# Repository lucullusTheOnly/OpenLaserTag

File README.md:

# OpenLaserTag
OperLaserTag is a DIY system for the popular game lasertag. I have designed it for high flexibility for game modes. With this article series and a little knowledge about electronics with microcontrollers like the Arduino you should be able to build your own lasertag system.
The work on this project isn't finished jet and I would be glad to receive some honest hints about what the system should be able to do and how this can be accomplished.

The System consists of the Arduino-based tagger, which is connected to a smartphone via bluetooth. The tagger uses an infrared LED and a lens to send a beam of modulated IR-light in the direction the tagger is pointed to. This works similar to normal IR-remotes, for example for your TV. The tagger is connected to a number of receiver modules, which are located on a vest, so that you can be hit by other players with their tagger. The Arduino informs the smartphone whenever something happens via a bluetooth-serial module and the smartphone does all the management of the game.

At the current state the tagger systems of different players don't have any contact. I designed the system, so that the game follows rules written in a XML-file and will end in a given time limit. This gives great flexibility, because you don't have to set up a communication system over the whole game field (which may be quite big). But this feature (over a limited range) could be added using 433MHz transmission modules.

For more information please visit the Wiki.

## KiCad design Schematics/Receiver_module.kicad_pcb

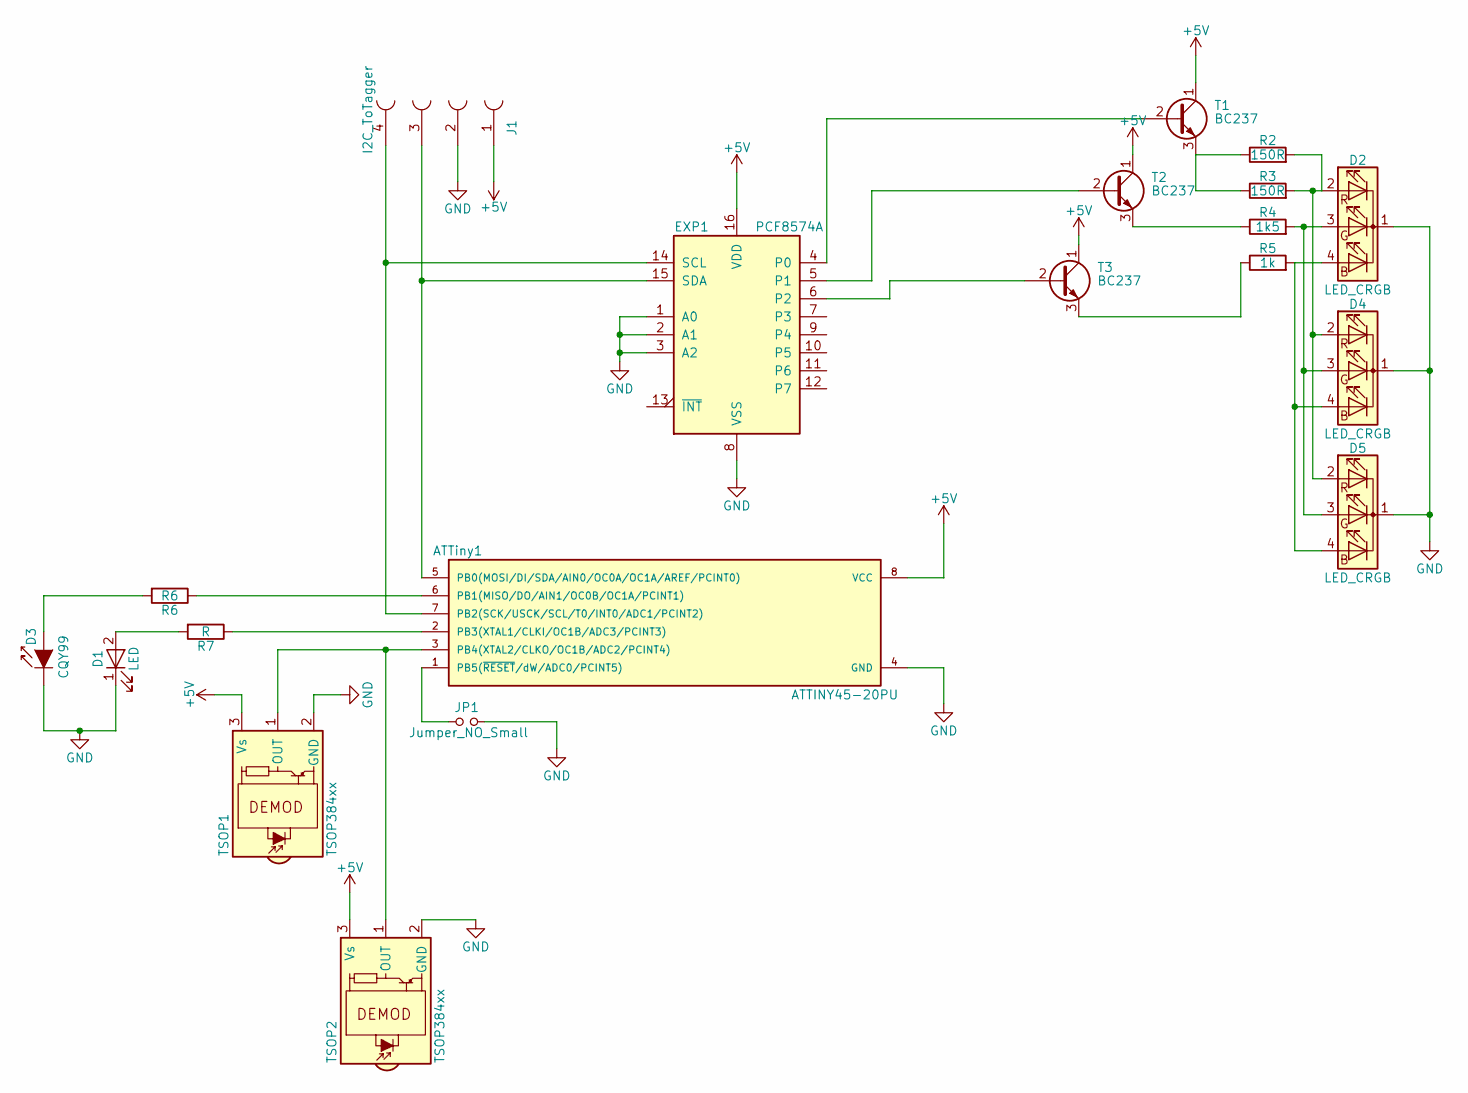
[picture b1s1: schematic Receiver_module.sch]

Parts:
ATTiny1: ATTINY45-20PU; DIP-8_W7.62mm
D1: LED; LED_D5.0mm_FlatTop
D2, D4, D5: LED_CRGB; LED_D5.0mm-4
D3: CQY99; LED_D5.0mm_FlatTop
EXP1: PCF8574A; DIP-16_W7.62mm_Socket
J1: I2C_ToTagger; SDL-104-X-XX_2x02
JP1: Jumper_NO_Small; Pin_Header_Straight_1x02_Pitch2.54mm
R2, R3: 150R; R_Axial_DIN0204_L3.6mm_D1.6mm_P2.54mm_Vertical
R4: 1k5; R_Axial_DIN0204_L3.6mm_D1.6mm_P2.54mm_Vertical
R5: 1k; R_Axial_DIN0204_L3.6mm_D1.6mm_P2.54mm_Vertical
R6: R6; R_Axial_DIN0204_L3.6mm_D1.6mm_P2.54mm_Vertical
R7: R; R_Axial_DIN0204_L3.6mm_D1.6mm_P2.54mm_Vertical
T1, T2, T3: BC237; TO-92_Inline_Narrow_Oval
TSOP1, TSOP2: TSOP384xx; IRReceiver_Vishay_MINICAST-3pin

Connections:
+5V: ATTiny1.8 (VCC), EXP1.16 (VDD), J1.1, T1.1 (C), T2.1 (C), T3.1 (C), TSOP1.3 (Vs), TSOP2.3 (Vs)
GND: ATTiny1.4 (GND), D1.1 (K), D2.1 (K), D3.1 (K), D4.1 (K), D5.1 (K), EXP1.1 (A0), EXP1.2 (A1), EXP1.3 (A2), EXP1.8 (VSS), J1.2, JP1.2, TSOP1.2 (GND), TSOP2.2 (GND)
unnamed: ATTiny1.1 (PB5(~RESET~/dW/ADC0/PCINT5)), JP1.1
unnamed: ATTiny1.2 (PB3(XTAL1/CLKI/OC1B/ADC3/PCINT3)), R7.1
unnamed: ATTiny1.3 (PB4(XTAL2/CLKO/OC1B/ADC2/PCINT4)), TSOP1.1 (OUT), TSOP2.1 (OUT)
unnamed: ATTiny1.5 (PB0(MOSI/DI/SDA/AIN0/OC0A/OC1A/AREF/PCI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), EXP1.15 (SDA), J1.3
unnamed: ATTiny1.6 (PB1(MISO/DO/AIN1/OC0B/OC1A/PCINT1)), R6.1
unnamed: ATTiny1.7 (PB2(SCK/USCK/SCL/T0/INT0/ADC1/PCINT2)), EXP1.14 (SCL), J1.4
unnamed: D1.2 (A), R7.2
unnamed: D2.2 (RA), D4.2 (RA), D5.2 (RA), R2.2, R3.2
unnamed: D2.3 (GA), D4.3 (GA), D5.3 (GA), R4.2
unnamed: D2.4 (BA), D4.4 (BA), D5.4 (BA), R5.2
unnamed: D3.2 (A), R6.2
unnamed: EXP1.4 (P0), T1.2 (B)
unnamed: EXP1.5 (P1), T2.2 (B)
unnamed: EXP1.6 (P2), T3.2 (B)
unnamed: R2.1, R3.1, T1.3 (E)
unnamed: R4.1, T2.3 (E)
unnamed: R5.1, T3.3 (E)

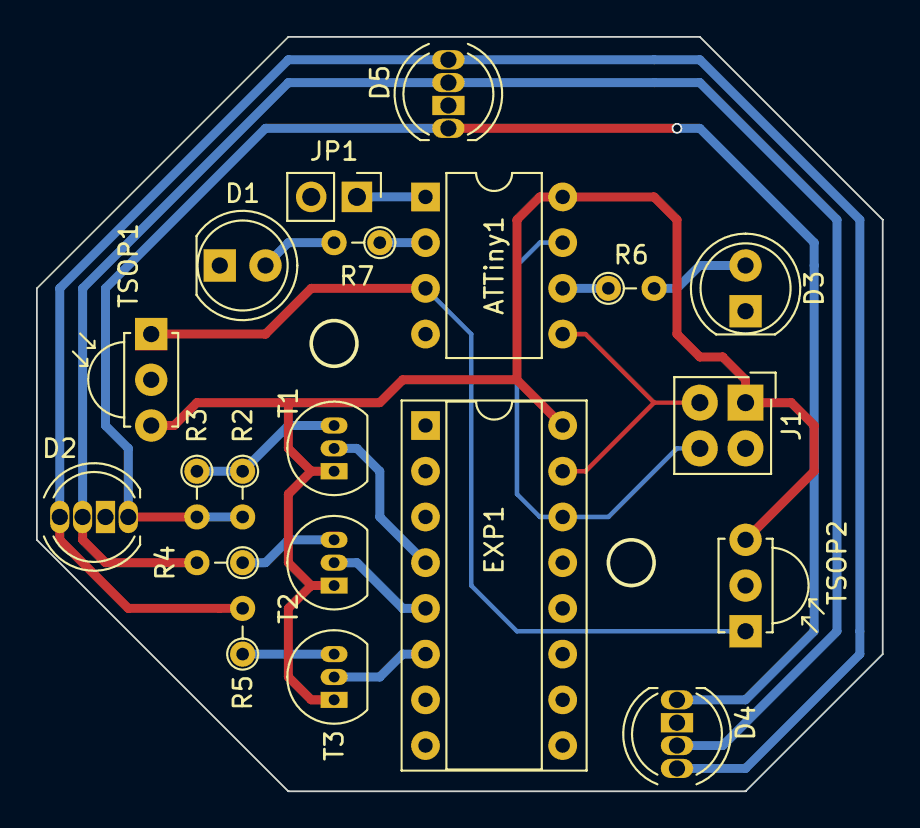
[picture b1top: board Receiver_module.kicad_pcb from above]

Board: 2 copper layers, 47.0 x 41.9 mm, 20 parts (0 on the bottom side), 19 nets.

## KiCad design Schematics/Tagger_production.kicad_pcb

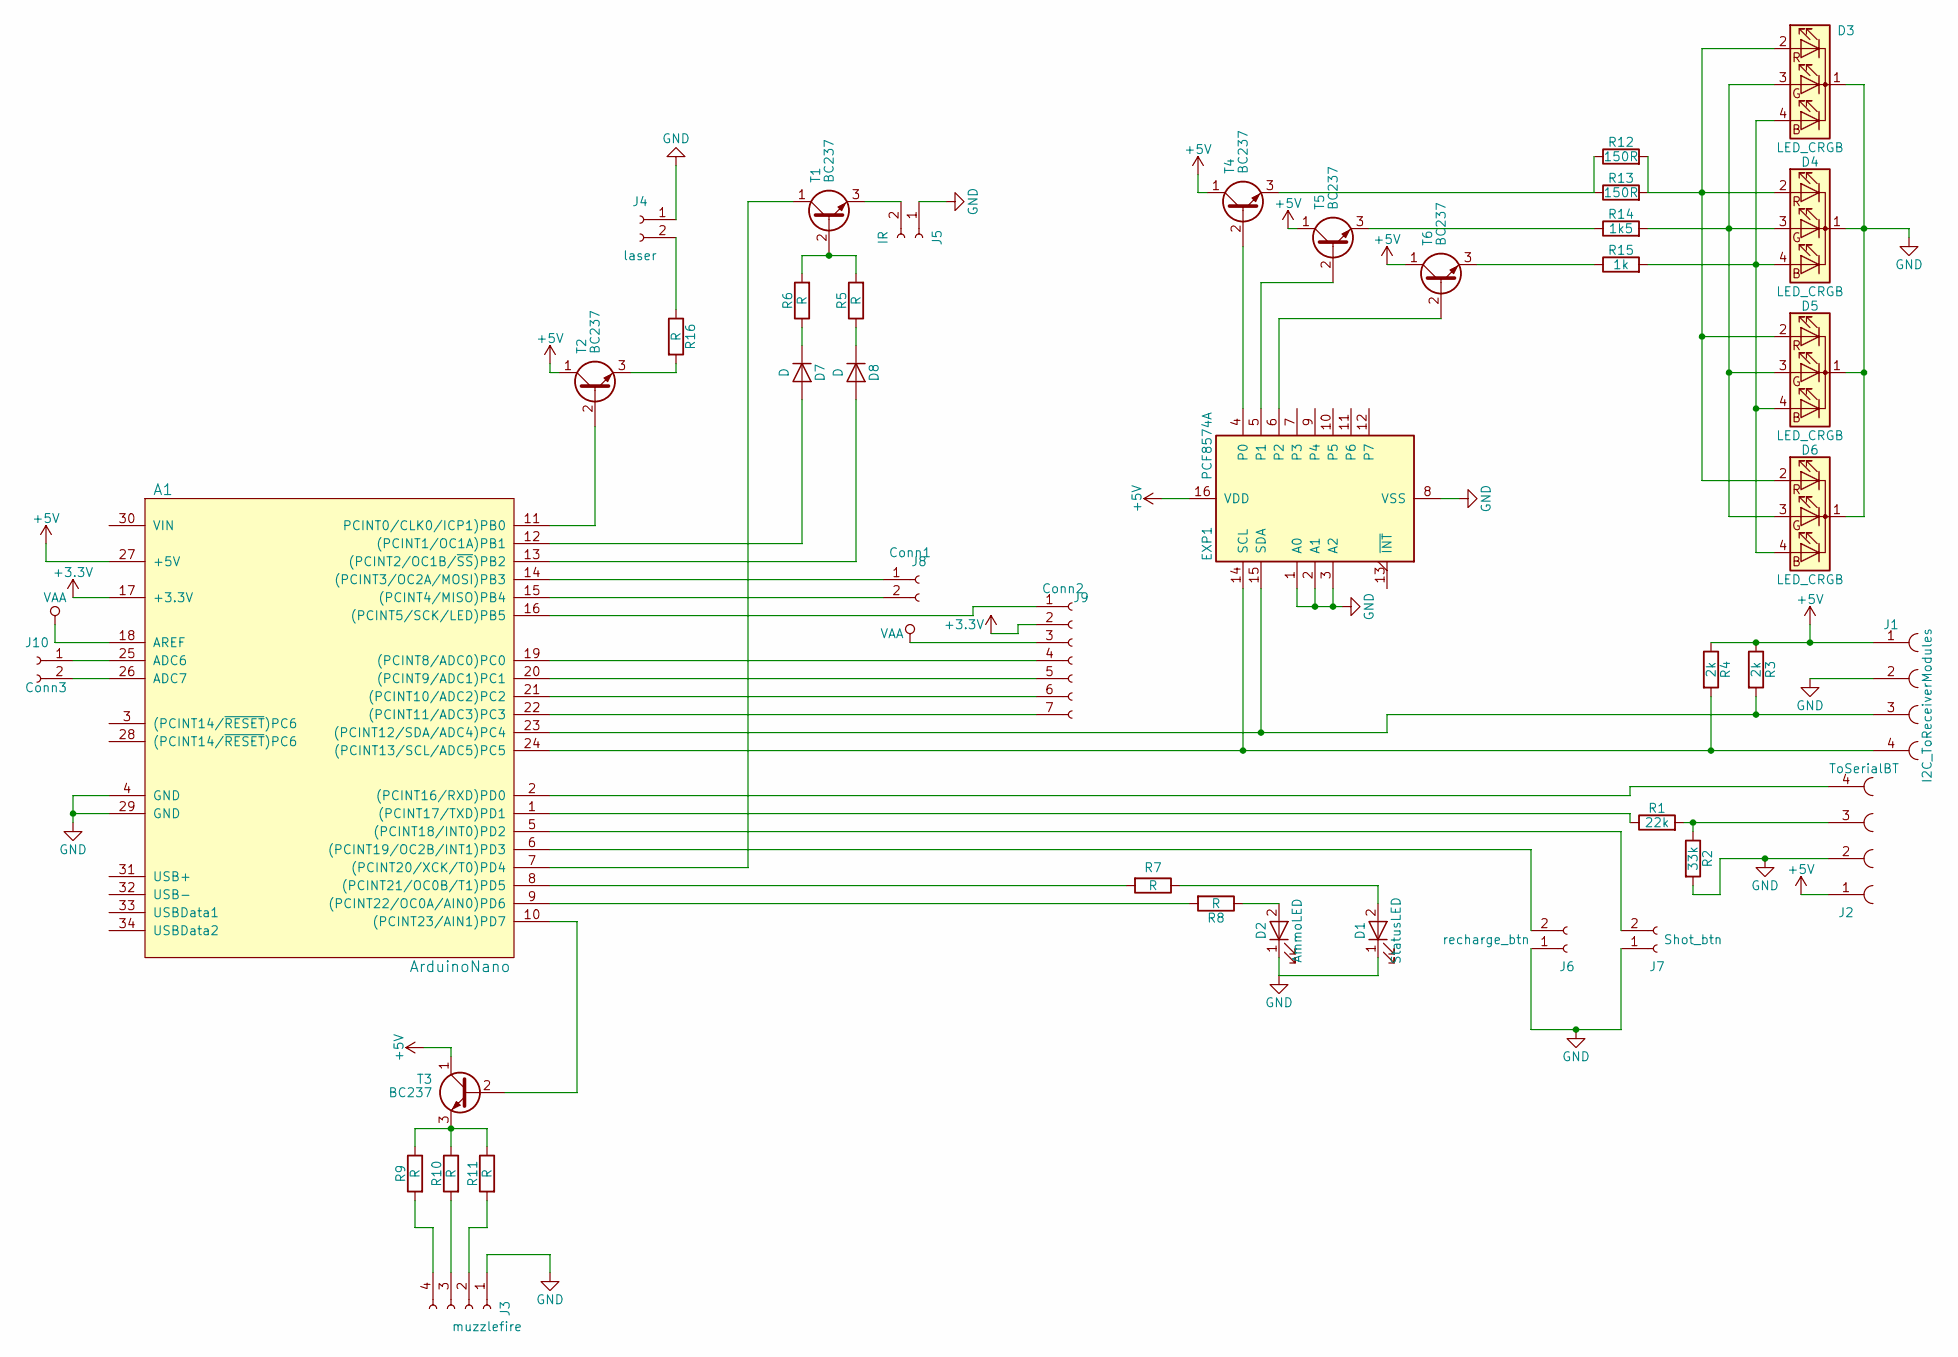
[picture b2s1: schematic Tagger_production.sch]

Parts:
A1: ArduinoNano
D1: StatusLED; LED_D5.0mm_FlatTop
D2: AmmoLED; LED_D5.0mm_FlatTop
D3, D4, D5, D6: LED_CRGB; LED_D5.0mm-4
D7, D8: D; D_A-405_P2.54mm_Vertical_KathodeUp
EXP1: PCF8574A; DIP-16_W7.62mm
J1: I2C_ToReceiverModules; SDL-104-X-XX_2x02
J2: ToSerialBT; Socket_Strip_Angled_1x04_Pitch2.54mm
J3: muzzlefire; Socket_Strip_Straight_1x04_Pitch2.54mm
J4: laser; Socket_Strip_Straight_1x02_Pitch2.54mm
J5: IR; Socket_Strip_Straight_1x02_Pitch2.54mm
J6: recharge_btn; Socket_Strip_Straight_1x02_Pitch2.54mm
J7: Shot_btn; Socket_Strip_Straight_1x02_Pitch2.54mm
J8: Conn1; Socket_Strip_Straight_1x02_Pitch2.54mm
J9: Conn2; Socket_Strip_Straight_1x07_Pitch2.54mm
J10: Conn3; Socket_Strip_Straight_1x02_Pitch2.54mm
R1: 22k; R_Axial_DIN0207_L6.3mm_D2.5mm_P2.54mm_Vertical
R2: 33k; R_Axial_DIN0207_L6.3mm_D2.5mm_P2.54mm_Vertical
R3, R4: 2k; R_Axial_DIN0207_L6.3mm_D2.5mm_P2.54mm_Vertical
R5, R6, R7, R8, R9, R10, R11, R16: R; R_Axial_DIN0207_L6.3mm_D2.5mm_P2.54mm_Vertical
R12, R13: 150R; R_Axial_DIN0207_L6.3mm_D2.5mm_P2.54mm_Vertical
R14: 1k5; R_Axial_DIN0207_L6.3mm_D2.5mm_P2.54mm_Vertical
R15: 1k; R_Axial_DIN0207_L6.3mm_D2.5mm_P2.54mm_Vertical
T1, T2, T3, T4, T5, T6: BC237; TO-92_Inline_Narrow_Oval

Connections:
+3V3: A1.17 (+3.3V), J9.2
+5V: A1.27 (+5V), EXP1.16 (VDD), J1.1, J2.1, R3.1, R4.1, T2.1 (C), T3.1 (C), T4.1 (C), T5.1 (C), T6.1 (C)
GND: A1.4 (GND), A1.29 (GND), D1.1 (K), D2.1 (K), D3.1 (K), D4.1 (K), D5.1 (K), D6.1 (K), EXP1.1 (A0), EXP1.2 (A1), EXP1.3 (A2), EXP1.8 (VSS), J1.2, J2.2, J3.1, J4.1, J5.1, J6.1, J7.1, R2.2
unnamed: A1.1 ((PCINT17/TXD)PD1), R1.1
unnamed: A1.2 ((PCINT16/RXD)PD0), J2.4
unnamed: A1.5 ((PCINT18/INT0)PD2), J7.2
unnamed: A1.6 ((PCINT19/OC2B/INT1)PD3), J6.2
unnamed: A1.7 ((PCINT20/XCK/T0)PD4), T1.1 (C)
unnamed: A1.8 ((PCINT21/OC0B/T1)PD5), R7.2
unnamed: A1.9 ((PCINT22/OC0A/AIN0)PD6), R8.2
unnamed: A1.10 ((PCINT23/AIN1)PD7), T3.2 (B)
unnamed: A1.11 (PCINT0/CLK0/ICP1)PB0), T2.2 (B)
unnamed: A1.12 ((PCINT1/OC1A)PB1), D7.2 (A)
unnamed: A1.13 ((PCINT2/OC1B/~SS~)PB2), D8.2 (A)
unnamed: A1.14 ((PCINT3/OC2A/MOSI)PB3), J8.1
unnamed: A1.15 ((PCINT4/MISO)PB4), J8.2
unnamed: A1.16 ((PCINT5/SCK/LED)PB5), J9.1
unnamed: A1.19 ((PCINT8/ADC0)PC0), J9.4
unnamed: A1.20 ((PCINT9/ADC1)PC1), J9.5
unnamed: A1.21 ((PCINT10/ADC2)PC2), J9.6
unnamed: A1.22 ((PCINT11/ADC3)PC3), J9.7
unnamed: A1.23 ((PCINT12/SDA/ADC4)PC4), EXP1.15 (SDA), J1.3, R3.2
unnamed: A1.24 ((PCINT13/SCL/ADC5)PC5), EXP1.14 (SCL), J1.4, R4.2
unnamed: A1.25 (ADC6), J10.1
unnamed: A1.26 (ADC7), J10.2
unnamed: D1.2 (A), R7.1
unnamed: D2.2 (A), R8.1
unnamed: D3.2 (RA), D4.2 (RA), D5.2 (RA), D6.2 (RA), R12.2, R13.2
unnamed: D3.3 (GA), D4.3 (GA), D5.3 (GA), D6.3 (GA), R14.2
unnamed: D3.4 (BA), D4.4 (BA), D5.4 (BA), D6.4 (BA), R15.2
unnamed: D7.1 (K), R6.1
unnamed: D8.1 (K), R5.1
unnamed: EXP1.4 (P0), T4.2 (B)
unnamed: EXP1.5 (P1), T5.2 (B)
unnamed: EXP1.6 (P2), T6.2 (B)
unnamed: J2.3, R1.2, R2.1
unnamed: J3.2, R11.2
unnamed: J3.3, R10.2
unnamed: J3.4, R9.2
unnamed: J4.2, R16.1
unnamed: J5.2, T1.3 (E)
unnamed: R5.2, R6.2, T1.2 (B)
unnamed: R9.1, R10.1, R11.1, T3.3 (E)
unnamed: R12.1, R13.1, T4.3 (E)
unnamed: R14.1, T5.3 (E)
unnamed: R15.1, T6.3 (E)
unnamed: R16.2, T2.3 (E)
VAA: A1.18 (AREF), J9.3

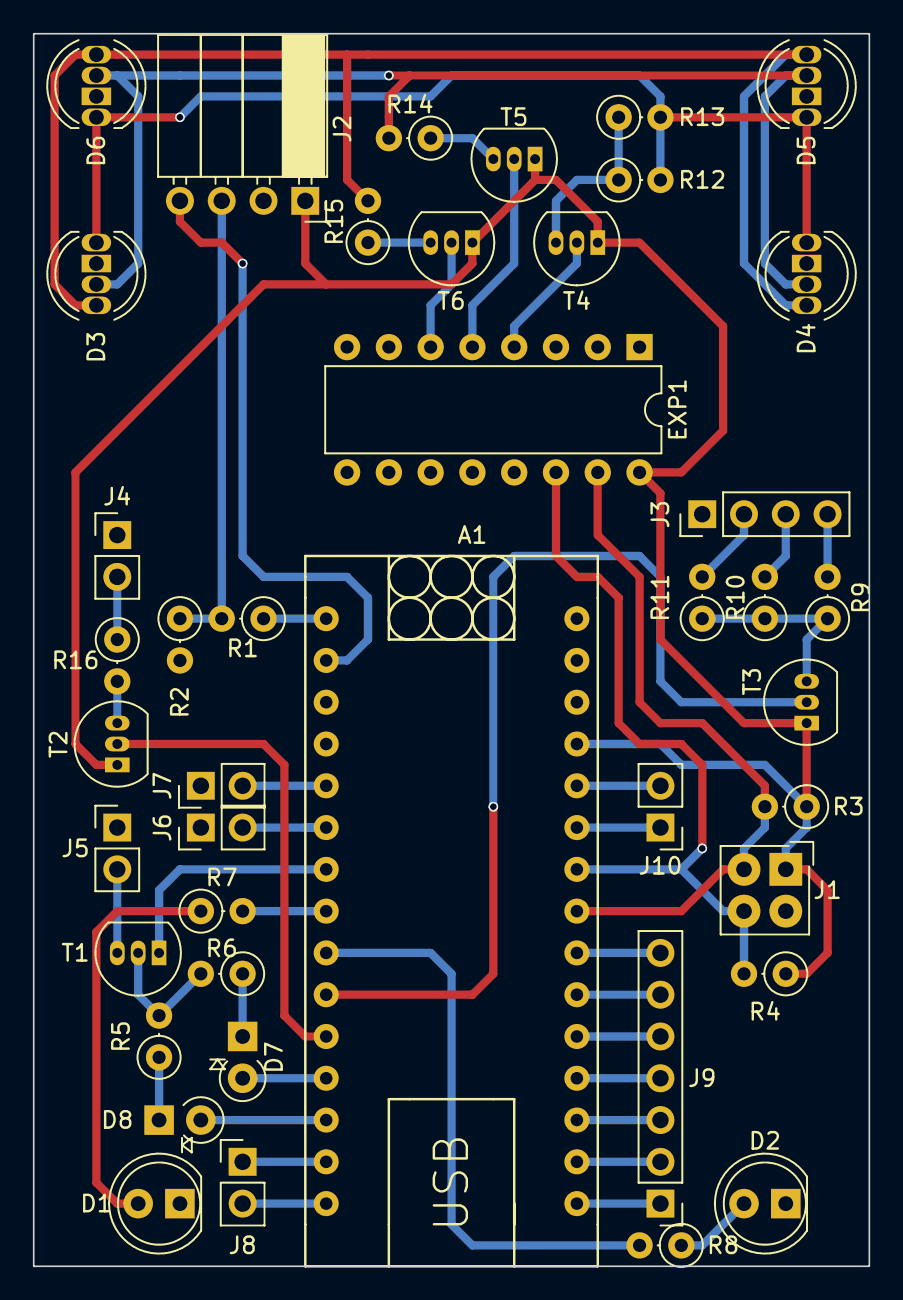
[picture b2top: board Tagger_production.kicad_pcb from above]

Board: 2 copper layers, 50.8 x 74.9 mm, 42 parts (0 on the bottom side), 48 nets.

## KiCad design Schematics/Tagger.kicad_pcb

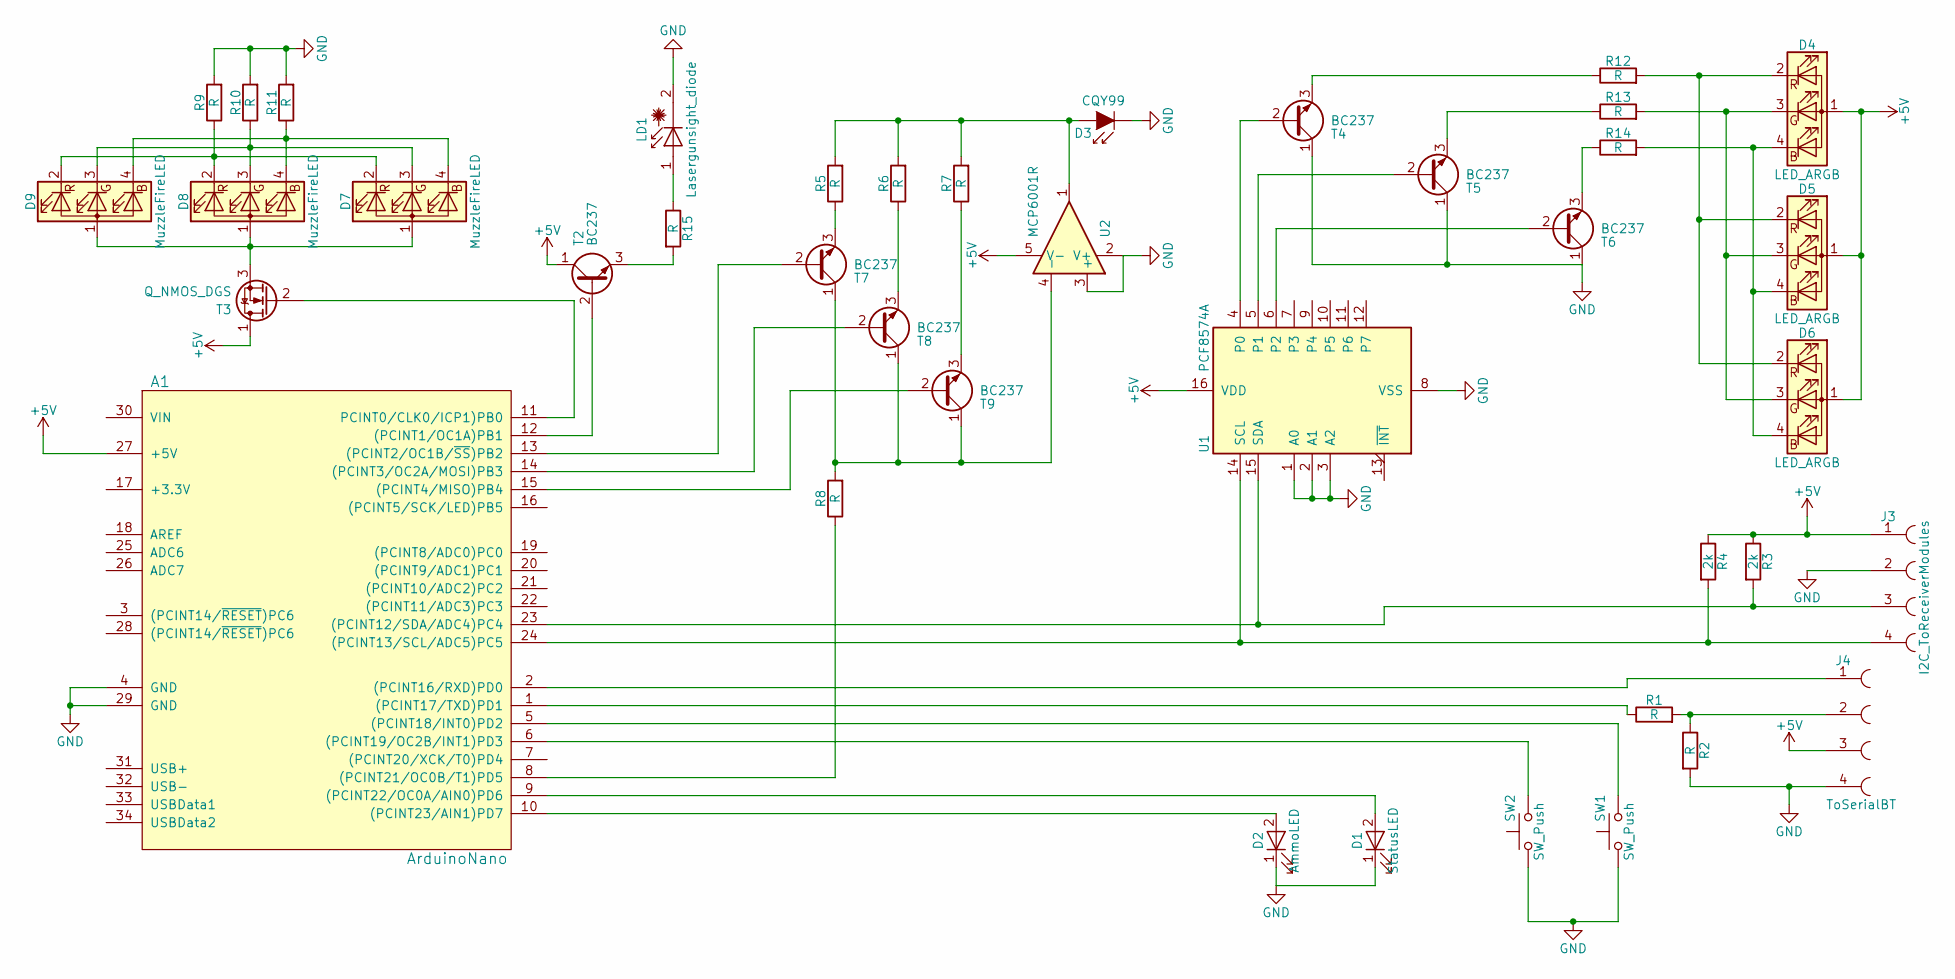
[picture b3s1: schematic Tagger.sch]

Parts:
A1: ArduinoNano
D1: StatusLED; LED_D5.0mm_FlatTop
D2: AmmoLED; LED_D5.0mm_FlatTop
D3: CQY99; LED_D5.0mm_FlatTop
D4, D5, D6: LED_ARGB; LED_D5.0mm-4
D7, D8, D9: MuzzleFireLED; LED_D5.0mm-4
J3: I2C_ToReceiverModules; SDL-104-X-XX_2x02
J4: ToSerialBT; Pin_Header_Angled_1x04_Pitch2.54mm
LD1: Lasergunsight_diode; Pin_Header_Straight_1x02_Pitch2.54mm
R1, R2, R5, R6, R7, R8, R9, R10, R11, R12, R13, R14, R15: R; R_Axial_DIN0207_L6.3mm_D2.5mm_P2.54mm_Vertical
R3, R4: 2k; R_Axial_DIN0207_L6.3mm_D2.5mm_P2.54mm_Vertical
SW1, SW2: SW_Push; Pin_Header_Straight_1x02_Pitch2.54mm
T2, T4, T5, T6, T7, T8, T9: BC237; TO-92_Molded_Narrow
T3: Q_NMOS_DGS; TO-126_Vertical
U1: PCF8574A; DIP-16_W7.62mm
U2: MCP6001R; DIP-8_W7.62mm

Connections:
+5V: A1.27 (+5V), D4.1 (A), D5.1 (A), D6.1 (A), J3.1, J4.3, R3.1, R4.1, T2.1 (C), T3.1 (D), U1.16 (VDD), U2.5 (V-)
GND: A1.4 (GND), A1.29 (GND), D1.1 (K), D2.1 (K), D3.1 (K), J3.2, J4.4, LD1.2 (K), R2.2, R9.2, R10.2, R11.2, SW1.1, SW2.1, T4.1 (C), T5.1 (C), T6.1 (C), U1.1 (A0), U1.2 (A1), U1.3 (A2), U1.8 (VSS), U2.2 (V+), U2.3 (+)
unnamed: A1.1 ((PCINT17/TXD)PD1), R1.1
unnamed: A1.2 ((PCINT16/RXD)PD0), J4.1
unnamed: A1.5 ((PCINT18/INT0)PD2), SW1.2
unnamed: A1.6 ((PCINT19/OC2B/INT1)PD3), SW2.2
unnamed: A1.8 ((PCINT21/OC0B/T1)PD5), R8.1
unnamed: A1.9 ((PCINT22/OC0A/AIN0)PD6), D1.2 (A)
unnamed: A1.10 ((PCINT23/AIN1)PD7), D2.2 (A)
unnamed: A1.11 (PCINT0/CLK0/ICP1)PB0), T3.2 (G)
unnamed: A1.12 ((PCINT1/OC1A)PB1), T2.2 (B)
unnamed: A1.13 ((PCINT2/OC1B/~SS~)PB2), T7.2 (B)
unnamed: A1.14 ((PCINT3/OC2A/MOSI)PB3), T8.2 (B)
unnamed: A1.15 ((PCINT4/MISO)PB4), T9.2 (B)
unnamed: A1.23 ((PCINT12/SDA/ADC4)PC4), J3.3, R3.2, U1.15 (SDA)
unnamed: A1.24 ((PCINT13/SCL/ADC5)PC5), J3.4, R4.2, U1.14 (SCL)
unnamed: D3.2 (A), R5.2, R6.2, R7.2, U2.1
unnamed: D4.2 (RK), D5.2 (RK), D6.2 (RK), R12.2
unnamed: D4.3 (GK), D5.3 (GK), D6.3 (GK), R13.2
unnamed: D4.4 (BK), D5.4 (BK), D6.4 (BK), R14.2
unnamed: D7.1 (A), D8.1 (A), D9.1 (A), T3.3 (S)
unnamed: D7.2 (RK), D8.2 (RK), D9.2 (RK), R9.1
unnamed: D7.3 (GK), D8.3 (GK), D9.3 (GK), R10.1
unnamed: D7.4 (BK), D8.4 (BK), D9.4 (BK), R11.1
unnamed: J4.2, R1.2, R2.1
unnamed: LD1.1 (A), R15.1
unnamed: R5.1, T7.3 (E)
unnamed: R6.1, T8.3 (E)
unnamed: R7.1, T9.3 (E)
unnamed: R8.2, T7.1 (C), T8.1 (C), T9.1 (C), U2.4 (-)
unnamed: R12.1, T4.3 (E)
unnamed: R13.1, T5.3 (E)
unnamed: R14.1, T6.3 (E)
unnamed: R15.2, T2.3 (E)
unnamed: T4.2 (B), U1.4 (P0)
unnamed: T5.2 (B), U1.5 (P1)
unnamed: T6.2 (B), U1.6 (P2)

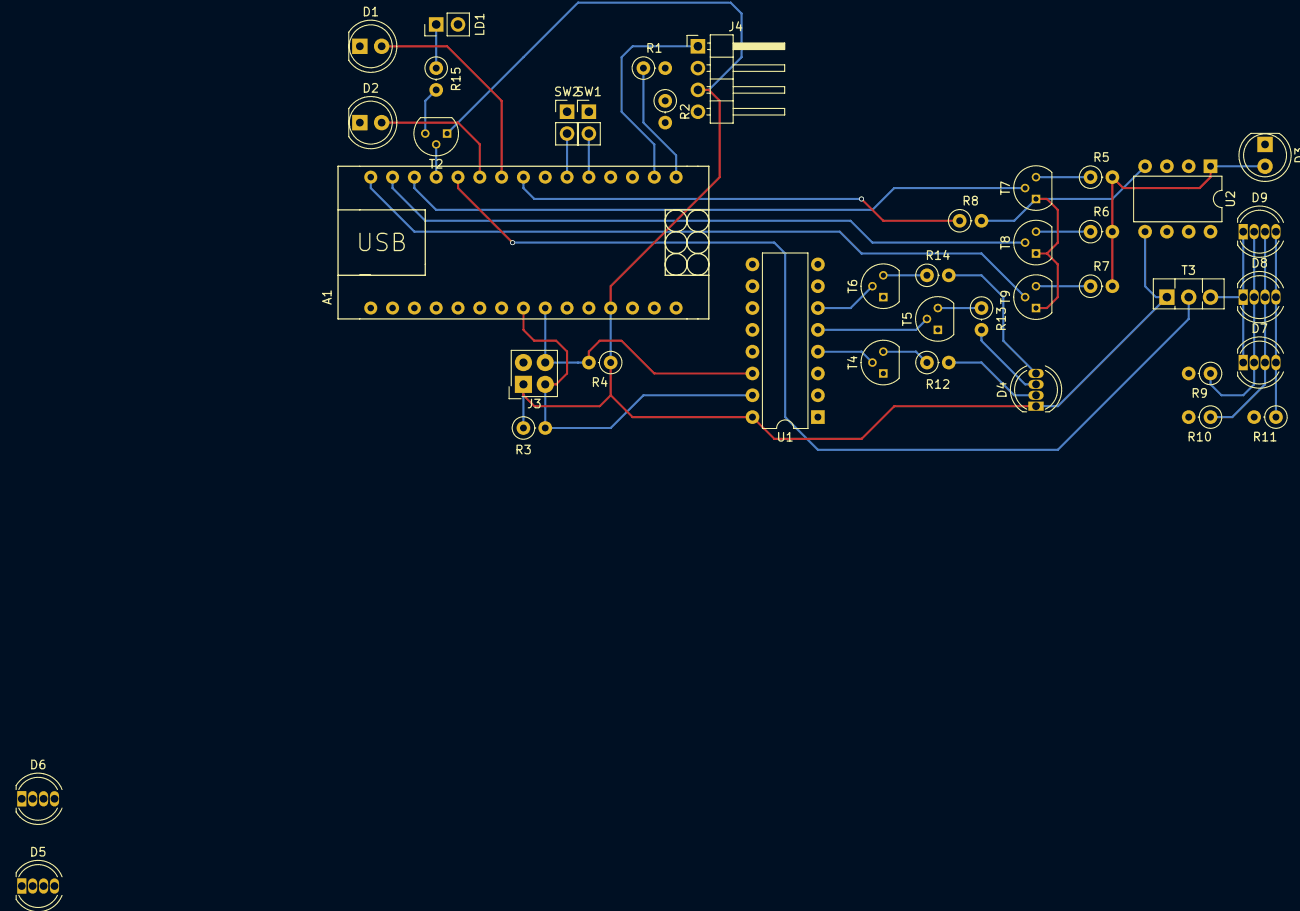
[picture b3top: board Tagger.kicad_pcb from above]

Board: 2 copper layers, 40 parts (0 on the bottom side), 37 nets.

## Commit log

2018-01-14 Add Description
2018-01-14 Added images for wiki
2018-02-03 New Version of Tagger/Receiver Schematics and PCBs
